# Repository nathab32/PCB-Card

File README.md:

# PCB Card

This is a PCB Business Card I made for Fallout! It has a simple circuit powered by a CR2032 Button Cell, and various silkscreen graphics. The circuit just blinks two LEDS on and off.

## BOM

| Reference | Qty | Value | Link |
| --- | --- | --- | --- |
| C1,C2 | 2 | 22uF | https://www.lcsc.com/datasheet/lcsc_datasheet_2304140030_Samsung-Electro-Mechanics-CL10A226MQ8NRNC_C59461.pdf |
| D1,D2 | 2 | Green | https://www.lcsc.com/datasheet/lcsc_datasheet_1806151820_Hubei-KENTO-Elec-KT-0805G_C2297.pdf |
| Q1,Q2 | 2 | 2SA812 | https://wmsc.lcsc.com/wmsc/upload/file/pdf/v2/lcsc/2312221203_hongjiacheng-2SA812_C7420323.pdf |
| R1,R2 | 2 | 100 | https://www.lcsc.com/datasheet/lcsc_datasheet_2411221126_UNI-ROYAL-Uniroyal-Elec-0805W8F1000T5E_C17408.pdf |
| R3,R4 | 2 | 100k | https://www.lcsc.com/datasheet/lcsc_datasheet_2205312316_UNI-ROYAL-Uniroyal-Elec-0805W8F1003T5E_C149504.pdf |
| S1 | 1 | Tactile Button, 160gf | https://www.lcsc.com/datasheet/lcsc_datasheet_2304140030_XKB-Connection-TS-1187A-B-A-B_C318884.pdf |

Slack: @nathab

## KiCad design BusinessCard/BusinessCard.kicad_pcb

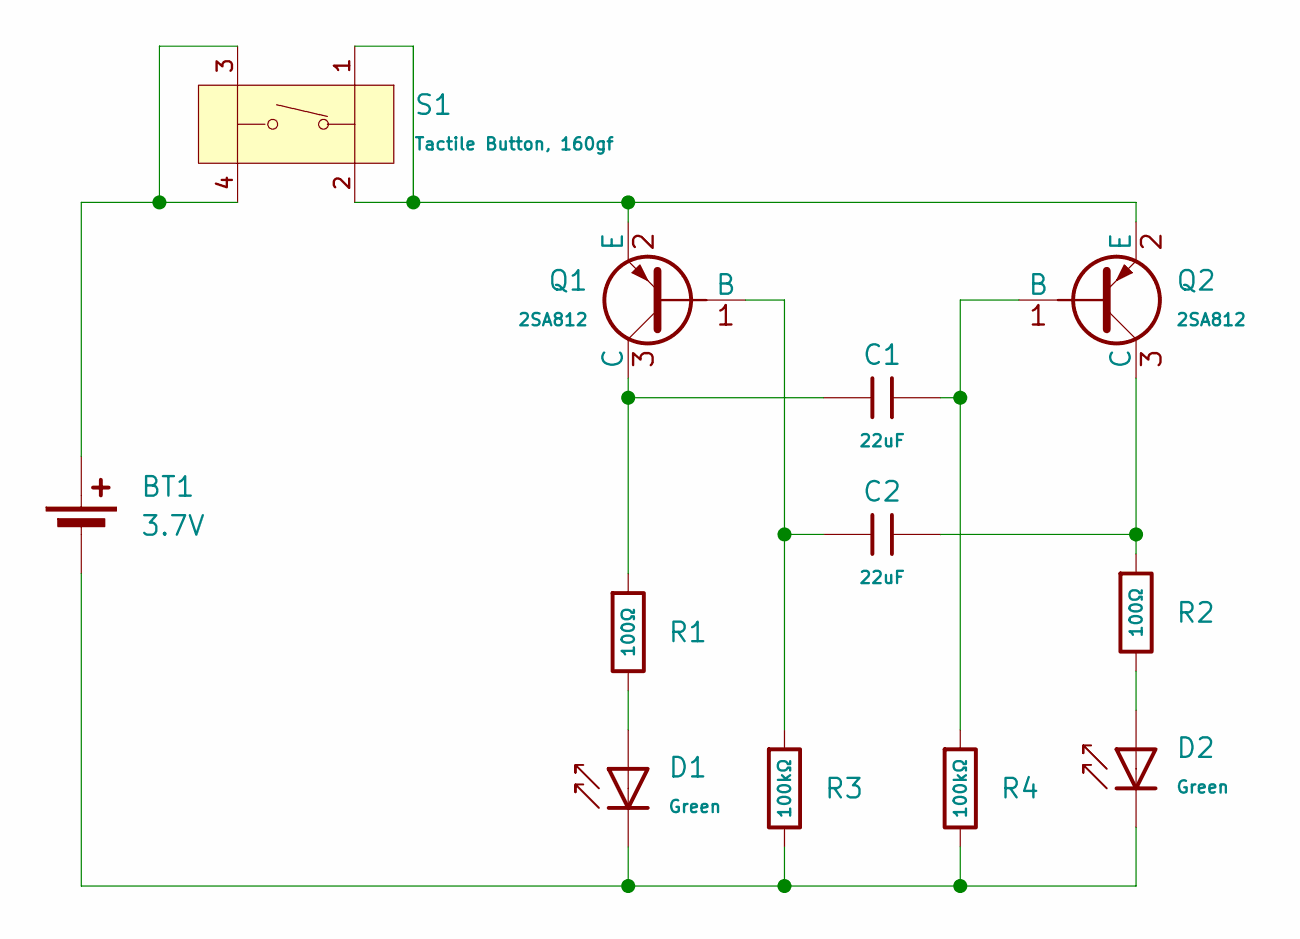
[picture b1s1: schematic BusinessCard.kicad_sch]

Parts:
BT1: 3.7V; CR2025 Circuit Board Battery Holder
C1, C2: 22uF; C_0603; Voltage Rated 6.3V; Tolerance ±20%; Part CL10A226MQ8NRNC; LCSC C59461
D1, D2: Green; D_0805; Part KT-0805G; LCSC C2297
Q1, Q2: 2SA812; Q_SOT-23; Part 2SA812; LCSC C7420323
R1, R2: 100Ω; R_0805; Overload Voltage (Max) 150V; Tolerance ±1%; Part 0805W8F1000T5E; LCSC C17408
R3, R4: 100kΩ; R_0805; Overload Voltage (Max) 150V; Tolerance ±1%; Part 0805W8F1003T5E; LCSC C149504
S1: Tactile Button, 160gf; SW-SMD_4P-L5.1-W5.1-P3.70-LS6.5-TL-2; Voltage Rating (Dc) 12V; Part TS-1187A-B-A-B; LCSC C318884

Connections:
unnamed: BT1.1 (+), S1.3 (C), S1.4 (D)
unnamed: BT1.2 (-), D1.1, D2.1, R3.2, R4.2
unnamed: D1.2, R1.2
unnamed: D2.2, R2.2
unnamed: C2.1, Q1.1 (B), R3.1
unnamed: C1.1, Q1.3 (C), R1.1
unnamed: Q1.2 (E), Q2.2 (E), S1.1 (A), S1.2 (B)
unnamed: C1.2, Q2.1 (B), R4.1
unnamed: C2.2, Q2.3 (C), R2.1

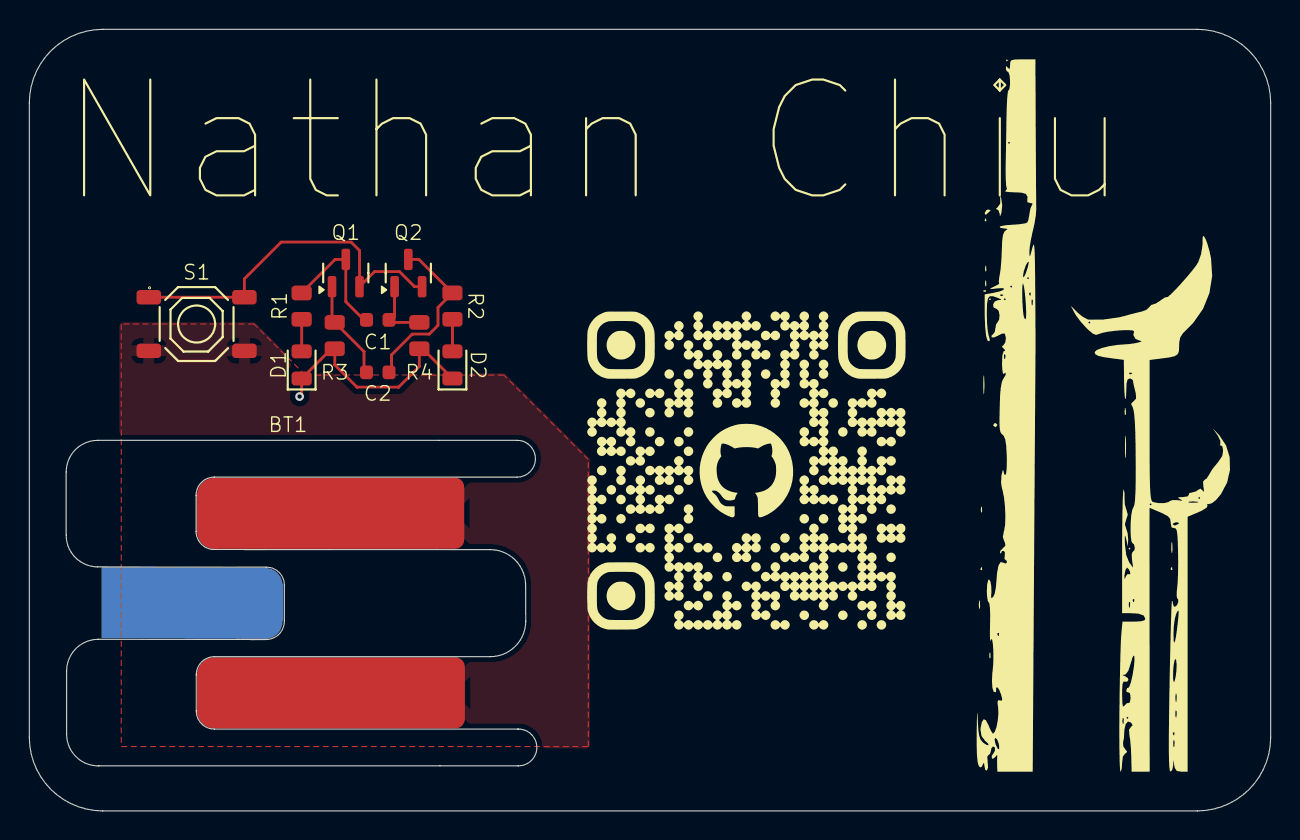
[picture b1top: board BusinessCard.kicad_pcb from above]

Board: 2 copper layers, 85.7 x 54.0 mm, 12 parts (0 on the bottom side), 9 nets.

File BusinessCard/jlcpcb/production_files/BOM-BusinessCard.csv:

Comment,Designator,Footprint,LCSC,Quantity
100kΩ,"R3,R4",R_0805,C149504,2
100Ω,"R1,R2",R_0805,C17408,2
22uF,"C1,C2",C_0603,C59461,2
2SA812,"Q1,Q2",Q_SOT-23,C7420323,2
Green,"D1,D2",D_0805,C2297,2
"Tactile Button, 160gf",S1,SW-SMD_4P-L5.1-W5.1-P3.70-LS6.5-TL-2,C318884,1
